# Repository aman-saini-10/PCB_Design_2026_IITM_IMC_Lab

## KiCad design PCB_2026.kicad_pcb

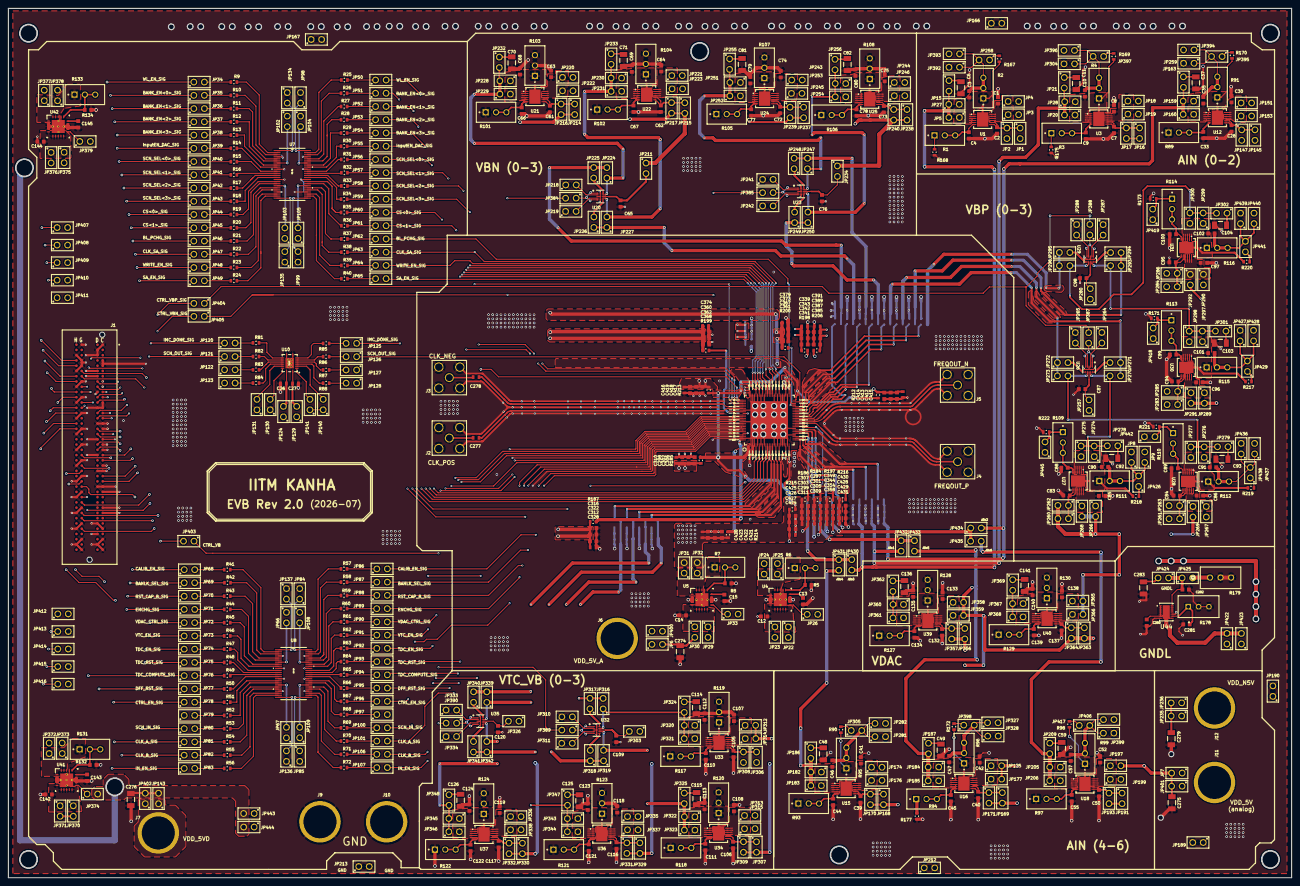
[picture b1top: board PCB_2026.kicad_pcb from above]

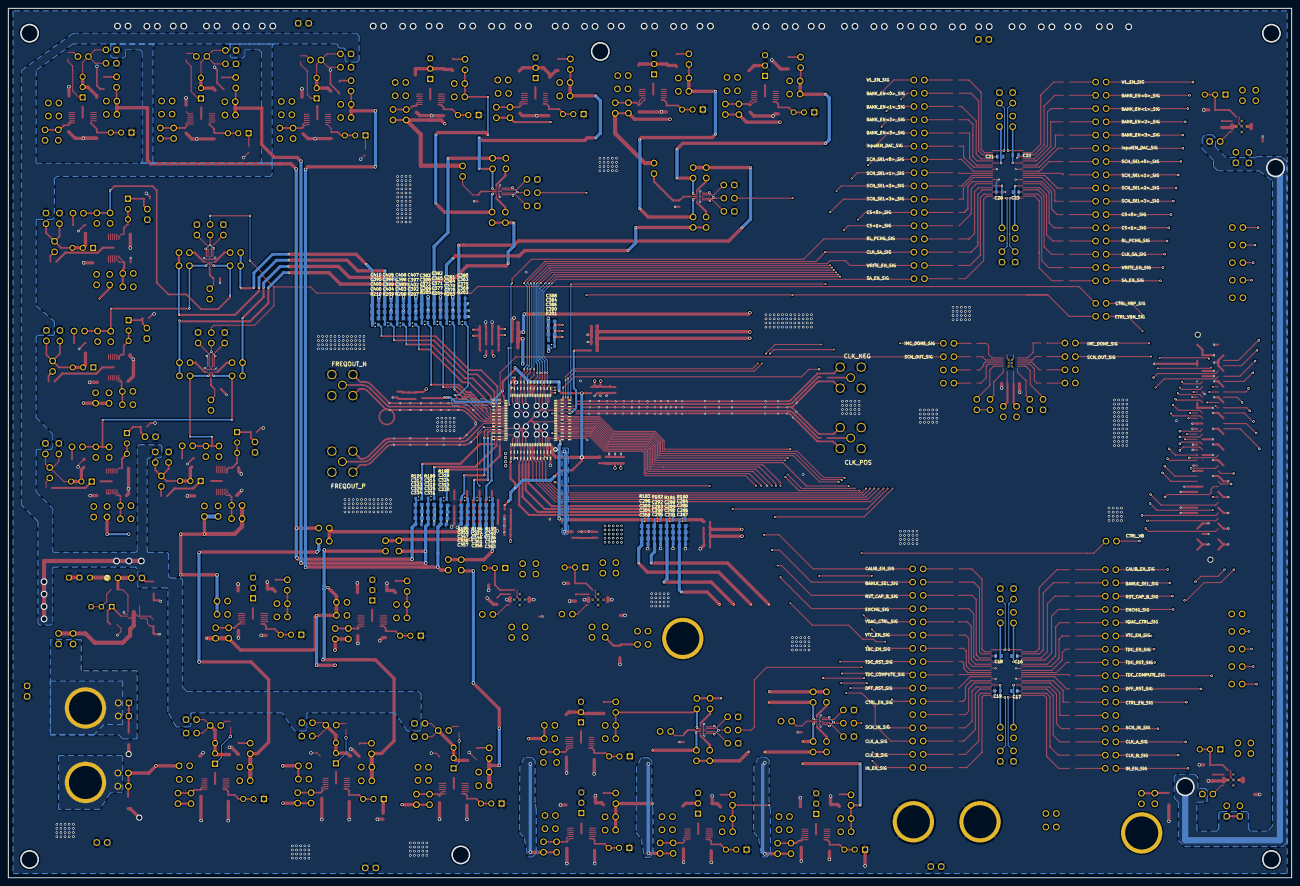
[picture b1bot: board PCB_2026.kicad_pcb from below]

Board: 4 copper layers, 310.0 x 210.0 mm, 859 parts (103 on the bottom side), 512 nets.

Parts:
C1, C3, C8, C10, C30, C35, C41, C42, C46, C47, C52, C57, C63, C64, C68, C69, C74, C75, C79, C80, C85, C86, C90, C91, C96, C97, C101, C102, C107, C108, C112, C113, C118, C119, C123, C124, C133, C135, C138, C140, C280, C282: 10u; CAPC1608X90N
C2, C7, C12, C14, C28, C39, C40, C50, C61, C62, C72, C73, C83, C84, C94, C95, C105, C106, C116, C117, C132, C137, C142, C144: 4.7u; CAPC1608X90N
C4, C9, C33, C44, C45, C55, C65, C66, C67, C76, C77, C78, C87, C88, C89, C98, C99, C100, C109, C110, C111, C120, C121, C122, C134, C139, C281, C285, C289, C293, C300, C301, C302, C303, C316, C318, C319, C323, C340, C341, C346, C347, C349, C362, C367, C369, C370, C371, C372, C386, C387, C397, C398, C399, C400, C413, C418, C421, C426, C429: 100n; CAPC1608X90N
C6, C11, C37, C48, C49, C59, C70, C71, C81, C82, C92, C93, C103, C104, C114, C115, C125, C126, C136, C141, C274, C275, C276, C279, C283: C100u; CAPC3216X180N
C13, C15, C143, C145, C286, C290, C294, C304, C305, C306, C307, C322, C324, C325, C329, C342, C348, C351, C352, C354, C368, C373, C375, C376, C377, C378, C388, C389, C402, C403, C404, C405, C414, C417, C422, C425, C430: 1n; CAPC1608X90N
C16, C17, C18, C19, C20, C21, C22, C23, C26, C27: 1uF; CAPC1608X90N
C277, C278, C287, C291, C295, C308, C309, C310, C311, C328, C330, C331, C334, C339, C353, C356, C357, C358, C374, C379, C380, C381, C382, C383, C390, C391, C407, C408, C409, C410, C415, C416, C420, C424, C431: 1u; CAPC1608X90N
C284, C288, C292, C296, C297, C298, C299, C312, C313, C314, C317, C336, C337, C338, C343, C344, C360, C361, C363, C364, C365, C366, C384, C385, C392, C393, C394, C395, C412, C419, C423, C427, C428: 10n; CAPC1608X90N
J1: ASP-134603-01; CONN160_4603-01_SAI
J2, J3, J4, J5: 142-0701-201; CONN_142-0701-201_CIN
J6, J7, J9, J10, J11, J12: BJACK
JP1, JP2, JP3, JP4, JP5, JP6, JP7, JP8, JP9, JP15, JP16, JP17, JP18, JP19, JP20, JP21, JP22, JP23, JP24, JP25, JP26, JP27, JP28, JP29, JP30, JP31, JP32, JP33, JP34, JP35, JP36, JP37, JP38, JP39, JP40, JP41, JP42, JP43, JP44, JP45, JP46, JP47, JP48, JP49, JP50, JP51, JP52, JP53, JP54, JP55, JP56, JP57, JP58, JP59, JP60, JP61, JP62, JP63, JP64, JP65, JP66, JP67, JP68, JP69, JP70, JP71, JP72, JP73, JP74, JP75, JP76, JP77, JP78, JP79, JP80, JP81, JP82, JP83, JP84, JP85, JP86, JP87, JP88, JP89, JP90, JP91, JP92, JP93, JP94, JP95, JP96, JP97, JP98, JP99, JP100, JP101, JP102, JP103, JP104, JP105, JP106, JP107, JP108, JP109, JP120, JP121, JP122, JP123, JP124, JP125, JP126, JP127, JP128, JP129, JP130, JP131, JP134, JP135, JP136, JP137, JP140, JP141, JP143, JP145, JP147, JP151, JP153, JP159, JP160, JP163, JP166, JP167, JP168, JP169, JP170, JP171, JP174, JP175, JP176, JP177, JP182, JP183, JP184, JP185, JP186, JP187, JP189, JP190, JP191, JP193, JP197, JP199, JP205, JP206, JP209, JP211, JP212, JP213, JP214, JP215, JP216, JP217, JP218, JP219, JP220, JP221, JP222, JP223, JP224, JP225, JP226, JP227, JP228, JP229, JP230, JP231, JP232, JP233, JP234, JP235, JP236, JP237, JP238, JP239, JP240, JP241, JP242, JP243, JP244, JP245, JP246, JP247, JP248, JP249, JP250, JP251, JP252, JP253, JP254, JP255, JP256, JP257, JP258, JP259, JP260, JP261, JP262, JP263, JP264, JP265, JP266, JP267, JP268, JP269, JP270, JP271, JP272, JP273, JP274, JP275, JP276, JP277, JP278, JP279, JP280, JP281, JP282, JP283, JP284, JP285, JP286, JP287, JP288, JP289, JP290, JP291, JP292, JP293, JP294, JP295, JP296, JP297, JP298, JP299, JP300, JP301, JP302, JP303, JP304, JP305, JP306, JP307, JP308, JP309, JP310, JP311, JP312, JP313, JP314, JP315, JP316, JP317, JP318, JP319, JP320, JP321, JP322, JP323, JP324, JP325, JP326, JP327, JP328, JP329, JP330, JP331, JP332, JP333, JP334, JP335, JP336, JP337, JP338, JP339, JP340, JP341, JP342, JP343, JP344, JP345, JP346, JP347, JP348, JP356, JP357, JP358, JP359, JP360, JP361, JP362, JP363, JP364, JP365, JP366, JP367, JP368, JP369, JP370, JP371, JP372, JP373, JP374, JP375, JP376, JP377, JP378, JP379, JP384, JP385, JP387, JP388, JP389, JP390, JP392, JP393, JP394, JP395, JP396, JP397, JP398, JP399, JP400, JP401, JP402, JP403, JP404, JP405, JP406, JP407, JP408, JP409, JP410, JP411, JP412, JP413, JP414, JP415, JP416, JP417, JP418, JP419, JP422, JP423, JP424, JP425, JP426, JP427, JP428, JP429, JP430, JP431, JP432, JP433, JP434, JP435, JP436, JP437, JP438, JP439, JP440, JP441, JP442, JP443, JP444, JP445: Jumper; 61300211121
R1, R3, R89, R93, R109, R110, R113, R114: 5kOhms; TRIM_PV36W253C01B00
R2, R4, R91, R95, R96, R99, R103, R104, R107, R108, R111, R112, R115, R116, R119, R120, R123, R124, R128, R130, R131, R133: 5kOhms; TRIM_PV36W502C01B00
R5, R8, R132, R134: 1kOhm; RESC1508X50N
R6: 2kOhms; TRIM_PV36W253C01B00
R7: 200 Ohms; TRIM_PV36W253C01B00
R9, R10, R11, R12, R13, R14, R15, R16, R17, R18, R19, R20, R21, R22, R23, R24, R25, R26, R27, R28, R29, R30, R31, R32, R33, R34, R35, R36, R37, R38, R39, R40, R41, R42, R43, R44, R45, R46, R47, R48, R49, R50, R51, R52, R53, R54, R55, R56, R57, R58, R59, R60, R62, R63, R64, R65, R66, R67, R68, R69, R70, R71, R72, R81, R82, R83, R84, R85, R86, R87, R88: 10 ohm 1%; RES_ERJ3EKF10R0V
R61, R180, R181, R182, R183, R184, R185, R186, R187, R188, R189, R191, R193, R194, R195, R197, R198, R199, R200, R201, R202, R203, R204, R205, R206, R207, R208, R209, R210, R212, R213, R214, R215, R216: 1 ohm 0603; RES_ERJ3EKF10R0V
R90, R98, R167, R169, R170, R172, R217, R218, R219, R220: 10 ohm; RES_ERJ3EKF10R0V
R94, R97: 1kOhms; TRIM_PV36W253C01B00
R101, R102, R105, R106, R117, R118, R121, R122, R127, R129: 25kOhms; TRIM_PV36W253C01B00
R168: 5k ohm; RES_ERJ3EKF10R0V
R171, R173, R221, R222: 2k ohm; RES_ERJ3EKF10R0V
R175: 3k ohm; RES_ERJ3EKF10R0V
R177: 0.5k ohm; RES_ERJ3EKF10R0V
R178: PV36W203C01B00; POT_PV36W_MUR
R179: PV36W503C01B00; RES_PV36W503C01B00_BRN
U1, U3, U12, U15, U16, U18, U21, U22, U24, U25, U27, U28, U30, U31, U33, U34, U36, U37, U39, U40: LT3083EDF-PBF; DFN-12_DF_LIT
U4, U5, U41, U42: TPS74401RGWT; RGW0020A
U7, U8: SN74AVCH16T245GR; DGG48
U10: SN74AVC4T245RGYR; RGY16_2P55X2P05
U20, U23, U26, U29, U32, U35: TMUX1072RUTR; RUT0012A-MFG
U43: QFN100_0p8mm_lead
U44: LT3091EDE-TRPBF; DE_14_ADI

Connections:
/AIN0: C313.1, C318.1, C324.1, C330.1, JP5.2, JP15.2, JP27.1, JP430.2, R188.1
/AIN0_LS: C3.1, JP5.1, JP27.2, R2.1, R167.2, U1.1 (OUT), U1.2 (OUT), U1.3 (OUT), U1.4 (OUT), U1.5 (OUT), U1.13 (EPAD)
/AIN1: C314.1, C319.1, C325.1, C331.1, JP20.2, JP21.2, JP28.1, JP432.2, R189.1
/AIN1_LS: C10.1, JP20.1, JP28.2, R4.1, R169.2, U3.1 (OUT), U3.2 (OUT), U3.3 (OUT), U3.4 (OUT), U3.5 (OUT), U3.13 (EPAD)
/AIN2: C317.1, C323.1, C329.1, C334.1, JP159.2, JP160.1, JP163.2, JP434.2, R191.1
/AIN2_LS: C35.1, JP159.1, JP160.2, R91.1, R170.2, U12.1 (OUT), U12.2 (OUT), U12.3 (OUT), U12.4 (OUT), U12.5 (OUT), U12.13 (EPAD)
/AIN4: JP182.2, JP183.1, JP186.2, JP431.2
/AIN4_LS: C46.1, JP182.1, JP183.2, R90.2, R95.1, U15.1 (OUT), U15.2 (OUT), U15.3 (OUT), U15.4 (OUT), U15.5 (OUT), U15.13 (EPAD)
/AIN5: JP184.2, JP185.1, JP187.2, JP433.2
/AIN5_LS: C47.1, JP184.1, JP185.2, R96.1, R172.2, U16.1 (OUT), U16.2 (OUT), U16.3 (OUT), U16.4 (OUT), U16.5 (OUT), U16.13 (EPAD)
/AIN6: JP205.2, JP206.1, JP209.2, JP435.2
/AIN6_LS: C57.1, JP205.1, JP206.2, R98.2, R99.1, U18.1 (OUT), U18.2 (OUT), U18.3 (OUT), U18.4 (OUT), U18.5 (OUT), U18.13 (EPAD)
/BANK_EN<0>_Q: JP51.2, U43.13 (BANK_EN<0>)
/BANK_EN<0>_SIG: J1.11, JP35.1
/BANK_EN<1>_Q: JP52.2, U43.12 (BANK_EN<1>)
/BANK_EN<1>_SIG: J1.14, JP36.1
/BANK_EN<2>_Q: JP53.2, U43.11 (BANK_EN<2>)
/BANK_EN<2>_SIG: J1.15, JP37.1
/BANK_EN<3>_Q: JP54.2, U43.9 (BANK_EN<3>)
/BANK_EN<3>_SIG: J1.18, JP38.1
/BANK_SEL_Q: JP87.2, U43.97 (BANK_SEL)
/BANK_SEL_SIG: J1.58, JP69.1
/BL_PCHG_Q: JP62.2, U43.51 (BL_PCHG)
/BL_PCHG_SIG: J1.22, JP46.1
/CALIB_EN_Q: JP86.2, U43.98 (CALIB_EN)
/CALIB_EN_SIG: J1.57, JP68.1
/CLK_+: C277.2, U43.81 (CLK_POS)
/CLK_-: C278.2, U43.80 (CLK_NEG)
/CLK_A_Q: JP101.2, U43.79 (CLK_A)
/CLK_A_SIG: J1.104, JP81.1
/CLK_B_Q: JP106.2, U43.78 (CLK_B)
/CLK_B_SIG: J1.105, JP82.1
/CLK_SA_Q: JP63.2, U43.57 (CLK_SA_B)
/CLK_SA_SIG: J1.23, JP47.1
/CLK_conn_+: C277.1, J2.1
/CLK_conn_-: C278.1, J3.1
/CS<0>_Q: JP60.2, U43.67 (CS<0>)
/CS<0>_SIG: J1.54, JP44.1
/CS<1>_Q: JP61.2, U43.65 (CS<1>)
/CS<1>_SIG: J1.55, JP45.1
/CTRL_EN_Q: JP96.2, U43.85 (CTRL_EN)
/CTRL_EN_SIG: J1.102, JP78.1
/CTRL_VB: JP389.2, JP390.2, JP403.1
/CTRL_VBN: JP384.2, JP385.2, JP405.1
/CTRL_VBN_SIG: J1.116, JP405.2
/CTRL_VBP: JP387.2, JP388.2, JP404.1
/CTRL_VBP_SIG: J1.114, JP404.2
/CTRL_VB_SIG: J1.113, JP403.2
/DFF_RST_Q: JP95.2, U43.86 (DFF_RST)
/DFF_RST_SIG: J1.92, JP77.1
/ENCHG_Q: JP89.2, U43.93 (CHG_EN)
/ENCHG_SIG: J1.61, JP71.1
/EN_U4: JP26.1, U4.11 (EN)
/EN_U5: JP33.1, U5.11 (EN)
/EN_U41: JP374.1, U41.11 (EN)
/EN_U42: JP379.1, U42.11 (EN)
/FREQOUT_N: J5.1, U43.37 (FreqOut_Neg)
/FREQOUT_P: J4.1, U43.36 (FreqOut_Pos)
/GNDL: C282.1, JP424.1, JP425.1, U44.11 (OUT), U44.12 (OUT), U44.13 (OUT), U44.14 (OUT)
/GNDL_BUF: C283.1, JP9.2, JP282.2, JP328.2, JP393.2, JP394.2, JP396.2, JP406.2, JP424.2, JP428.2, JP437.2, JP440.2
/GNDL_JP: JP425.2, R179.1
/H4: J1.124, JP407.1
/H5: J1.125, JP408.1
/H7: J1.127, JP409.1
/H8: J1.128, JP410.1
/H10: J1.130, JP411.1
/H11: J1.131, JP412.1
/H13: J1.133, JP413.1
/H14: J1.134, JP414.1
/H16: J1.136, JP415.1
/H17: J1.137, JP416.1
/IMC_DONE_Q: JP125.1, U43.95 (IMC_DONE)
/IMC_DONE_SIG: J1.110, JP120.1
/IN_EN_Q: JP107.2, U43.77 (IN_EN)
/IN_EN_SIG: J1.107, JP83.1
/InputEN_DAC_Q: JP55.2, U43.34 (InputEN_DAC)
/InputEN_DAC_SIG: J1.19, JP39.1
/RST_CAP_B_Q: JP88.2, U43.94 (RST_CAP_B)
/RST_CAP_B_SIG: J1.60, JP70.1
/SA_EN_Q: JP65.2, U43.69 (SA_EN_B)
/SA_EN_SIG: J1.27, JP49.1
/SCN_IN_Q: JP100.2, U43.76 (SCN_IN)
/SCN_IN_SIG: J1.108, JP80.1
/SCN_OUT_Q: JP126.1, U43.49 (SCN_OUT)
/SCN_OUT_SIG: J1.111, JP121.1
/SCN_SEL<0>_Q: JP56.2, U43.64 (SCN_SEL<0>)
/SCN_SEL<0>_SIG: J1.48, JP40.1
/SCN_SEL<1>_Q: JP57.2, U43.63 (SCN_SEL<1>)
/SCN_SEL<1>_SIG: J1.49, JP41.1
/SCN_SEL<2>_Q: JP58.2, U43.62 (SCN_SEL<2>)
/SCN_SEL<2>_SIG: J1.51, JP42.1
/SCN_SEL<3>_Q: JP59.2, U43.61 (SCN_SEL<3>)
/SCN_SEL<3>_SIG: J1.52, JP43.1
/TDC_COMPUTE_Q: JP94.2, U43.87 (TDC_COMPUTE)
/TDC_COMPUTE_SIG: J1.93, JP76.1
/TDC_EN_Q: JP92.2, U43.90 (TDC_EN)
/TDC_EN_SIG: J1.89, JP74.1
/TDC_RST_Q: JP93.2, U43.88 (TDC_RST_B)
/TDC_RST_SIG: J1.90, JP75.1
/U1_IN: C1.1, JP3.1, JP4.1, U1.9 (IN), U1.10 (IN), U1.11 (IN), U1.12 (IN)
/U1_SET: C4.2, R1.2, R1.3, U1.6 (SET)
/U1_VCONTROL: C2.1, JP1.1, JP2.1, U1.7 (VCONTROL), U1.8 (VCONTROL)
/U3_IN: C8.1, JP18.1, JP19.1, U3.9 (IN), U3.10 (IN), U3.11 (IN), U3.12 (IN)
/U3_SET: C9.2, R3.2, R3.3, U3.6 (SET)
/U3_VCONTROL: C7.1, JP16.1, JP17.1, U3.7 (VCONTROL), U3.8 (VCONTROL)
/U12_IN: C30.1, JP151.1, JP153.1, U12.9 (IN), U12.10 (IN), U12.11 (IN), U12.12 (IN)
/U12_SET: C33.2, R89.2, R89.3, U12.6 (SET)
/U12_VCONTROL: C28.1, JP145.1, JP147.1, U12.7 (VCONTROL), U12.8 (VCONTROL)
/U15_IN: C41.1, JP174.1, JP176.1, U15.9 (IN), U15.10 (IN), U15.11 (IN), U15.12 (IN)
/U15_SET: C44.2, R93.2, R93.3, U15.6 (SET)
/U15_VCONTROL: C39.1, JP168.1, JP170.1, U15.7 (VCONTROL), U15.8 (VCONTROL)
/U16_IN: C42.1, JP175.1, JP177.1, U16.9 (IN), U16.10 (IN), U16.11 (IN), U16.12 (IN)
/U16_SET: C45.2, R94.2, R94.3, U16.6 (SET)
/U16_VCONTROL: C40.1, JP169.1, JP171.1, U16.7 (VCONTROL), U16.8 (VCONTROL)
/U18_IN: C52.1, JP197.1, JP199.1, U18.9 (IN), U18.10 (IN), U18.11 (IN), U18.12 (IN)
/U18_SET: C55.2, R97.2, R97.3, U18.6 (SET)
/U18_VCONTROL: C50.1, JP191.1, JP193.1, U18.7 (VCONTROL), U18.8 (VCONTROL)
/U21_IN: C63.1, JP220.1, JP222.1, U21.9 (IN), U21.10 (IN), U21.11 (IN), U21.12 (IN)
/U21_OUT: C68.1, JP228.1, JP229.2, R103.1, U21.1 (OUT), U21.2 (OUT), U21.3 (OUT), U21.4 (OUT), U21.5 (OUT), U21.13 (EPAD)
/U21_SET: C66.2, R101.2, R101.3, U21.6 (SET)
/U21_VCONTROL: C61.1, JP214.1, JP216.1, U21.7 (VCONTROL), U21.8 (VCONTROL)
/U22_IN: C64.1, JP221.1, JP223.1, U22.9 (IN), U22.10 (IN), U22.11 (IN), U22.12 (IN)
/U22_OUT: C69.1, JP230.1, JP231.2, R104.1, U22.1 (OUT), U22.2 (OUT), U22.3 (OUT), U22.4 (OUT), U22.5 (OUT), U22.13 (EPAD)
/U22_SET: C67.2, R102.2, R102.3, U22.6 (SET)
/U22_VCONTROL: C62.1, JP215.1, JP217.1, U22.7 (VCONTROL), U22.8 (VCONTROL)
/U24_IN: C74.1, JP243.1, JP245.1, U24.9 (IN), U24.10 (IN), U24.11 (IN), U24.12 (IN)
/U24_OUT: C79.1, JP251.1, JP252.2, R107.1, U24.1 (OUT), U24.2 (OUT), U24.3 (OUT), U24.4 (OUT), U24.5 (OUT), U24.13 (EPAD)
/U24_SET: C77.2, R105.2, R105.3, U24.6 (SET)
/U24_VCONTROL: C72.1, JP237.1, JP239.1, U24.7 (VCONTROL), U24.8 (VCONTROL)
/U25_IN: C75.1, JP244.1, JP246.1, U25.9 (IN), U25.10 (IN), U25.11 (IN), U25.12 (IN)
/U25_OUT: C80.1, JP253.1, JP254.2, R108.1, U25.1 (OUT), U25.2 (OUT), U25.3 (OUT), U25.4 (OUT), U25.5 (OUT), U25.13 (EPAD)
/U25_SET: C78.2, R106.2, R106.3, U25.6 (SET)
/U25_VCONTROL: C73.1, JP238.1, JP240.1, U25.7 (VCONTROL), U25.8 (VCONTROL)
/U27_IN: C85.1, JP266.1, JP268.1, U27.9 (IN), U27.10 (IN), U27.11 (IN), U27.12 (IN)
/U27_OUT: C90.1, JP274.1, JP275.2, R111.1, R218.2, U27.1 (OUT), U27.2 (OUT), U27.3 (OUT), U27.4 (OUT), U27.5 (OUT), U27.13 (EPAD)
/U27_SET: C88.2, R109.2, R109.3, U27.6 (SET)
/U27_VCONTROL: C83.1, JP260.1, JP262.1, U27.7 (VCONTROL), U27.8 (VCONTROL)
/U28_IN: C86.1, JP267.1, JP269.1, U28.9 (IN), U28.10 (IN), U28.11 (IN), U28.12 (IN)
/U28_OUT: C91.1, JP276.1, JP277.2, R112.1, R219.2, U28.1 (OUT), U28.2 (OUT), U28.3 (OUT), U28.4 (OUT), U28.5 (OUT), U28.13 (EPAD)
/U28_SET: C89.2, R110.2, R110.3, U28.6 (SET)
/U28_VCONTROL: C84.1, JP261.1, JP263.1, U28.7 (VCONTROL), U28.8 (VCONTROL)
/U30_IN: C96.1, JP289.1, JP291.1, U30.9 (IN), U30.10 (IN), U30.11 (IN), U30.12 (IN)
/U30_OUT: C101.1, JP297.1, JP298.2, R115.1, R217.2, U30.1 (OUT), U30.2 (OUT), U30.3 (OUT), U30.4 (OUT), U30.5 (OUT), U30.13 (EPAD)
/U30_SET: C99.2, R113.2, R113.3, U30.6 (SET)
/U30_VCONTROL: C94.1, JP283.1, JP285.1, U30.7 (VCONTROL), U30.8 (VCONTROL)
/U31_IN: C97.1, JP290.1, JP292.1, U31.9 (IN), U31.10 (IN), U31.11 (IN), U31.12 (IN)
/U31_OUT: C102.1, JP299.1, JP300.2, R116.1, R220.2, U31.1 (OUT), U31.2 (OUT), U31.3 (OUT), U31.4 (OUT), U31.5 (OUT), U31.13 (EPAD)
/U31_SET: C100.2, R114.2, R114.3, U31.6 (SET)
/U31_VCONTROL: C95.1, JP284.1, JP286.1, U31.7 (VCONTROL), U31.8 (VCONTROL)
/U33_IN: C107.1, JP312.1, JP314.1, U33.9 (IN), U33.10 (IN), U33.11 (IN), U33.12 (IN)
/U33_OUT: C112.1, JP320.1, JP321.2, R119.1, U33.1 (OUT), U33.2 (OUT), U33.3 (OUT), U33.4 (OUT), U33.5 (OUT), U33.13 (EPAD)
/U33_SET: C110.2, R117.2, R117.3, U33.6 (SET)
/U33_VCONTROL: C105.1, JP306.1, JP308.1, U33.7 (VCONTROL), U33.8 (VCONTROL)
/U34_IN: C108.1, JP313.1, JP315.1, U34.9 (IN), U34.10 (IN), U34.11 (IN), U34.12 (IN)
/U34_OUT: C113.1, JP322.1, JP323.2, R120.1, U34.1 (OUT), U34.2 (OUT), U34.3 (OUT), U34.4 (OUT), U34.5 (OUT), U34.13 (EPAD)
/U34_SET: C111.2, R118.2, R118.3, U34.6 (SET)
/U34_VCONTROL: C106.1, JP307.1, JP309.1, U34.7 (VCONTROL), U34.8 (VCONTROL)
/U36_IN: C118.1, JP335.1, JP337.1, U36.9 (IN), U36.10 (IN), U36.11 (IN), U36.12 (IN)
/U36_OUT: C123.1, JP343.1, JP344.2, R123.1, U36.1 (OUT), U36.2 (OUT), U36.3 (OUT), U36.4 (OUT), U36.5 (OUT), U36.13 (EPAD)
/U36_SET: C121.2, R121.2, R121.3, U36.6 (SET)
/U36_VCONTROL: C116.1, JP329.1, JP331.1, U36.7 (VCONTROL), U36.8 (VCONTROL)
/U37_IN: C119.1, JP336.1, JP338.1, U37.9 (IN), U37.10 (IN), U37.11 (IN), U37.12 (IN)
/U37_OUT: C124.1, JP345.1, JP346.2, R124.1, U37.1 (OUT), U37.2 (OUT), U37.3 (OUT), U37.4 (OUT), U37.5 (OUT), U37.13 (EPAD)
/U37_SET: C122.2, R122.2, R122.3, U37.6 (SET)
/U37_VCONTROL: C117.1, JP330.1, JP332.1, U37.7 (VCONTROL), U37.8 (VCONTROL)
/U39_IN: C133.1, JP358.1, JP359.1, U39.9 (IN), U39.10 (IN), U39.11 (IN), U39.12 (IN)
/U39_OUT: C135.1, JP360.1, JP361.2, R128.1, U39.1 (OUT), U39.2 (OUT), U39.3 (OUT), U39.4 (OUT), U39.5 (OUT), U39.13 (EPAD)
/U39_SET: C134.2, R127.2, R127.3, U39.6 (SET)
/U39_VCONTROL: C132.1, JP356.1, JP357.1, U39.7 (VCONTROL), U39.8 (VCONTROL)
/U40_IN: C138.1, JP365.1, JP366.1, U40.9 (IN), U40.10 (IN), U40.11 (IN), U40.12 (IN)
/U40_OUT: C140.1, JP367.1, JP368.2, R130.1, U40.1 (OUT), U40.2 (OUT), U40.3 (OUT), U40.4 (OUT), U40.5 (OUT), U40.13 (EPAD)
/U40_SET: C139.2, R129.2, R129.3, U40.6 (SET)
/U40_VCONTROL: C137.1, JP363.1, JP364.1, U40.7 (VCONTROL), U40.8 (VCONTROL)
/U44_SET: C281.1, R178.1, U44.9 (SET)
/VB0: C284.1, C285.1, C286.1, C287.1, JP316.2, JP317.2, R180.1
/VB0_MUX: JP316.1, JP320.2, JP321.1, JP324.2, U32.10 (NC1)
/VB1: C288.1, C289.1, C290.1, C291.1, JP318.1, JP319.1, R181.1
/VB1_MUX: JP319.2, JP322.2, JP323.1, JP325.2, U32.8 (NC2)
/VB2: C292.1, C293.1, C294.1, C295.1, JP339.2, JP340.2, R182.1
/VB2_MUX: JP339.1, JP343.2, JP344.1, JP347.2, U35.10 (NC1)
/VB3: C296.1, C300.1, C304.1, C308.1, JP341.1, JP342.1, R183.1
/VB3_MUX: JP342.2, JP345.2, JP346.1, JP348.2, U35.8 (NC2)
/VBN0: C363.1, C369.1, C375.1, C380.1, JP224.2, JP225.2, R202.1
/VBN0_MUX: JP224.1, JP228.2, JP229.1, JP232.2, U20.10 (NC1)
/VBN0_q: R202.2, U43.39 (VBN<0>)
/VBN1: C364.1, C370.1, C376.1, C381.1, JP226.1, JP227.1, R203.1
/VBN1_MUX: JP227.2, JP230.2, JP231.1, JP233.2, U20.8 (NC2)
/VBN1_q: R203.2, U43.40 (VBN<1>)
/VBN2: C365.1, C371.1, C377.1, C382.1, JP247.2, JP248.2, R204.1
/VBN2_MUX: JP247.1, JP251.2, JP252.1, JP255.2, U23.10 (NC1)
/VBN2_q: R204.2, U43.41 (VBN<2>)
/VBN3: C366.1, C372.1, C378.1, C383.1, JP249.1, JP250.1, R205.1
/VBN3_MUX: JP250.2, JP253.2, JP254.1, JP256.2, U23.8 (NC2)
/VBN3_q: R205.2, U43.42 (VBN<3>)
/VBP0: C392.1, C397.1, C402.1, C407.1, JP270.2, JP271.2, R207.2
/VBP0_MUX: JP270.1, JP274.2, JP275.1, JP278.2, U26.10 (NC1)
/VBP0_q: R207.1, U43.43 (VBP<0>)
/VBP1: C393.1, C398.1, C403.1, C408.1, JP272.1, JP273.1, R208.2
/VBP1_MUX: JP273.2, JP276.2, JP277.1, JP279.2, U26.8 (NC2)
/VBP1_q: R208.1, U43.44 (VBP<1>)
/VBP2: C394.1, C399.1, C404.1, C409.1, JP293.2, JP294.2, R209.2
/VBP2_MUX: JP293.1, JP297.2, JP298.1, JP301.2, U29.10 (NC1)
/VBP2_q: R209.1, U43.45 (VBP<2>)
/VBP3: C395.1, C400.1, C405.1, C410.1, JP295.1, JP296.1, R210.2
/VBP3_MUX: JP296.2, JP299.2, JP300.1, JP302.2, U29.8 (NC2)
/VBP3_q: R210.1, U43.46 (VBP<3>)
/VCCA_DIG_LS: JP104.1, JP105.1, JP108.1, JP109.1, JP129.1, JP140.1, JP141.1, JP372.2, JP373.2
/VCCB_DIG_LS: JP66.1, JP67.1, JP102.1, JP103.1, JP124.1, JP377.2, JP378.2
/VDAC: C312.1, C316.1, C322.1, C328.1, C360.1, C361.1, C362.1, C367.1, C368.1, C373.1, C374.1, C379.1, JP360.2, JP361.1, JP362.2, JP367.2, JP368.1, JP369.2, R187.1, R199.2, R200.2
/VDAC_CTRL_Q: JP90.2, U43.92 (VDAC_CTRL)
/VDAC_CTRL_SIG: J1.86, JP72.1
/VDDA_0.9V: C297.1, C299.1, C301.1, C303.1, C305.1, C307.1, C309.1, C311.1, C339.1, C341.1, C342.1, C343.1, C344.1, C349.1, C354.1, C358.1, C384.1, C385.1, C386.1, C387.1, C388.1, C389.1, C390.1, C391.1, C420.1, C421.1, C422.1, C423.1, C428.1, C429.1, C430.1, C431.1, JP31.2, JP32.2, R184.1, R186.1, R197.2, R198.1, R201.2, R206.2, R214.1, R216.2
/VDDA_chip: R184.2, R186.2, R197.1, R198.2, R201.1, R206.1, R214.2, R216.1, U43.5 (vdda), U43.23 (vdda), U43.35 (vdda), U43.48 (vdda), U43.53 (vdda), U43.75 (vdda), U43.84 (vdda), U43.96 (vdda)
/VDDQ_1.8V: C298.1, C302.1, C306.1, C310.1, C412.1, C413.1, C414.1, C415.1, C416.1, C417.1, C418.1, C419.1, C424.1, C425.1, C426.1, C427.1, JP24.2, JP25.2, R185.1, R212.1, R213.1, R215.1
/VDDQ_chip: R185.2, R212.2, R213.2, R215.2, U43.1 (vddq), U43.25 (vddq), U43.50 (vddq), U43.71 (vddq)
/VDD_5V: C275.1, JP1.2, JP2.2, JP3.2, JP4.2, JP7.2, JP16.2, JP17.2, JP18.2, JP19.2, JP145.2, JP147.2, JP151.2, JP153.2, JP168.2, JP169.2, JP170.2, JP171.2, JP174.2, JP175.2, JP176.2, JP177.2, JP191.2, JP193.2, JP197.2, JP199.2, JP211.1, JP214.2, JP215.2, JP216.2, JP217.2, JP220.2, JP221.2, JP222.2, JP223.2, JP234.1, JP237.2, JP238.2, JP239.2, JP240.2, JP243.2, JP244.2, JP245.2, JP246.2, JP257.1, JP260.2, JP261.2, JP262.2, JP263.2, JP266.2, JP267.2, JP268.2, JP269.2, JP280.1, JP283.2, JP284.2, JP285.2, JP286.2, JP289.2, JP290.2, JP291.2, JP292.2, JP303.1, JP306.2, JP307.2, JP308.2, JP309.2, JP312.2, JP313.2, JP314.2, JP315.2, JP326.1, JP329.2, JP330.2, JP331.2, JP332.2, JP335.2, JP336.2, JP337.2, JP338.2, JP356.2, JP357.2, JP358.2, JP359.2, JP363.2, JP364.2, JP365.2, JP366.2, JP401.2, JP443.1, JP444.1
/VDD_5VD: C276.1, JP143.2, JP370.2, JP371.2, JP374.2, JP375.2, JP376.2, JP379.2, JP402.2, JP443.2, JP444.2
/VDD_5VD_JACK: J7.1, JP143.1, JP402.1
/VDD_5V_JACK: J11.1, JP7.1, JP401.1
/VDD_5V_U4: C12.1, JP22.1, JP23.1, U4.5 (IN), U4.6 (IN), U4.7 (IN), U4.8 (IN), U4.10 (BIAS)
/VDD_5V_U5: C14.1, JP29.1, JP30.1, U5.5 (IN), U5.6 (IN), U5.7 (IN), U5.8 (IN), U5.10 (BIAS)
/VDD_5V_U41: C142.1, JP370.1, JP371.1, U41.5 (IN), U41.6 (IN), U41.7 (IN), U41.8 (IN), U41.10 (BIAS)
/VDD_5V_U42: C144.1, JP375.1, JP376.1, U42.5 (IN), U42.6 (IN), U42.7 (IN), U42.8 (IN), U42.10 (BIAS)
/VDD_5V_a: C274.1, JP6.2, JP22.2, JP23.2, JP26.2, JP29.2, JP30.2, JP33.2, JP400.2
/VDD_5V_a_JACK: J6.1, JP6.1, JP400.1
/VDD_N5V: C279.1, JP235.2, JP236.2, JP422.1, JP423.1
/VDD_N5V_JACK: J12.1, JP235.1, JP236.1
/VFB_U4: R5.2, R6.2, R6.3, U4.16 (FB)
/VFB_U5: R7.2, R7.3, R8.2, U5.16 (FB)
/VFB_U41: R131.2, R131.3, R132.2, U41.16 (FB)
/VFB_U42: R133.2, R133.3, R134.2, U42.16 (FB)
/VIN_U44: C280.1, JP422.2, JP423.2, U44.1 (IN), U44.2 (IN), U44.3 (IN), U44.4 (IN), U44.5 (ILIM), U44.6 (IMONP), U44.8 (*SHDN), U44.15 (IN)
/VOUT_U4: JP24.1, JP25.1, R6.1, U4.1 (OUT), U4.18 (OUT), U4.19 (OUT), U4.20 (OUT)
/VOUT_U5: JP31.1, JP32.1, R7.1, U5.1 (OUT), U5.18 (OUT), U5.19 (OUT), U5.20 (OUT)
/VOUT_U41: JP372.1, JP373.1, R131.1, U41.1 (OUT), U41.18 (OUT), U41.19 (OUT), U41.20 (OUT)
/VOUT_U42: JP377.1, JP378.1, R133.1, U42.1 (OUT), U42.18 (OUT), U42.19 (OUT), U42.20 (OUT)
/VTC_EN_Q: JP91.2, U43.91 (VTC_EN)
/VTC_EN_SIG: J1.87, JP73.1
/WL_EN_Q: JP50.2, U43.7 (WL_EN)
/WL_EN_SIG: J1.10, JP34.1
/WRITE_EN_Q: JP64.2, U43.59 (WRITE_EN)
/WRITE_EN_SIG: J1.26, JP48.1
GND: C1.2, C2.2, C4.1, C6.2, C7.2, C8.2, C9.1, C11.2, C12.2, C13.2, C14.2, C15.2, C16.2, C17.2, C18.2, C19.2, C20.2, C21.2, C22.2, C23.2, C26.2, C27.2, C28.2, C30.2, C33.1, C37.2, C39.2, C40.2, C41.2, C42.2, C44.1, C45.1, C48.2, C49.2, C50.2, C52.2, C55.1, C59.2, C61.2, C62.2, C63.2, C64.2, C65.2, C66.1, C67.1, C68.2, C69.2, C70.2, C71.2, C72.2, C73.2, C74.2, C75.2, C76.2, C77.1, C78.1, C79.2, C80.2, C81.2, C82.2, C83.2, C84.2, C85.2, C86.2, C87.2, C88.1, C89.1, C92.2, C93.2, C94.2, C95.2, C96.2, C97.2, C98.2, C99.1, C100.1, C103.2, C104.2, C105.2, C106.2, C107.2, C108.2, C109.2, C110.1, C111.1, C112.2, C113.2, C114.2, C115.2, C116.2, C117.2, C118.2, C119.2, C120.2, C121.1, C122.1, C123.2, C124.2, C125.2, C126.2, C132.2, C133.2, C134.1, C135.2, C136.2, C137.2, C138.2, C139.1, C140.2, C141.2, C142.2, C143.2, C144.2, C145.2, C274.2, C275.2, C276.2, C279.2, C280.2, C281.2, C282.2, C283.2, C284.2, C285.2, C286.2, C287.2, C288.2, C289.2, C290.2, C291.2, C292.2, C293.2, C294.2, C295.2, C296.2, C297.2, C298.2, C299.2, C300.2, C301.2, C302.2, C303.2, C304.2, C305.2, C306.2, C307.2, C308.2, C309.2, C310.2, C311.2, C312.2, C313.2, C314.2, C316.2, C317.2, C318.2, C319.2, C322.2, C323.2, C324.2, C325.2, C328.2, C329.2, C330.2, C331.2, C334.2, C336.2, C337.2, C338.2, C339.2, C340.2, C341.2, C342.2, C343.2, C344.2, C346.2, C347.2, C348.2, C349.2, C351.2, C352.2, C353.2, C354.2, C356.2, C357.2, C358.2, C360.2, C361.2, C362.2, C363.2, C364.2, C365.2, C366.2, C367.2, C368.2, C369.2, C370.2, C371.2, C372.2, C373.2, C374.2, C375.2, C376.2, C377.2, C378.2, C379.2, C380.2, C381.2, C382.2, C383.2, C384.2, C385.2, C386.2, C387.2, C388.2, C389.2, C390.2, C391.2, C392.2, C393.2, C394.2, C395.2, C397.2, C398.2, C399.2, C400.2, C402.2, C403.2, C404.2, C405.2, C407.2, C408.2, C409.2, C410.2, C412.2, C413.2, C414.2, C415.2, C416.2, C417.2, C418.2, C419.2, C420.2, C421.2, C422.2, C423.2, C424.2, C425.2, C426.2, C427.2, C428.2, C429.2, C430.2, C431.2, J1.1, J1.4, J1.5, J1.8, J1.9, J1.12, J1.13, J1.16, J1.17, J1.20, J1.21, J1.24, J1.25, J1.28, J1.29, J1.32, J1.33, J1.36, J1.38, J1.40, J1.42, J1.43, J1.46, J1.47, J1.50, J1.53, J1.56, J1.59, J1.62, J1.65, J1.68, J1.75, J1.77, J1.79, J1.81, J1.84, J1.85, J1.88, J1.91, J1.94, J1.97, J1.100, J1.103, J1.106, J1.109, J1.112, J1.115, J1.118, J1.120, J1.123, J1.126, J1.129, J1.132, J1.135, J1.138, J1.141, J1.144, J1.147, J1.150, J1.153, J1.156, J1.159, J2.2, J2.3, J2.4, J2.5, J3.2, J3.3, J3.4, J3.5, J4.2, J4.3, J4.4, J4.5, J5.2, J5.3, J5.4, J5.5, J9.1, J10.1, JP8.2, JP84.2, JP85.2, JP98.2, JP99.2, JP130.1, JP131.1, JP134.1, JP135.1, JP136.1, JP137.1, JP166.1, JP166.2, JP167.1, JP167.2, JP189.1, JP189.2, JP190.1, JP190.2, JP212.1, JP212.2, JP213.1, JP213.2, JP218.1, JP219.1, JP241.1, JP242.1, JP259.2, JP264.1, JP265.1, JP281.2, JP287.1, JP288.1, JP304.2, JP310.1, JP311.1, JP327.2, JP333.1, JP334.1, JP392.2, JP399.2, JP418.1, JP419.1, JP427.2, JP436.2, JP439.2, JP442.1, JP445.1, R5.1, R8.1, R89.1, R93.1, R97.1, R101.1, R102.1, R103.2, R103.3, R104.2, R104.3, R105.1, R106.1, R107.2, R107.3, R108.2, R108.3, R117.1, R118.1, R119.2, R119.3, R120.2, R120.3, R121.1, R122.1, R123.2, R123.3, R124.2, R124.3, R127.1, R128.2, R128.3, R129.1, R130.2, R130.3, R132.1, R134.1, R168.2, R171.2, R173.2, R175.2, R177.1, R178.2, R178.3, R179.2, R179.3, R221.2, R222.2, U4.2 (NC), U4.3 (NC), U4.4 (NC), U4.12 (GND), U4.13 (NC), U4.14 (NC), U4.17 (NC), U4.21 (PAD), U5.2 (NC), U5.3 (NC), U5.4 (NC), U5.12 (GND), U5.13 (NC), U5.14 (NC), U5.17 (NC), U5.21 (PAD), U7.4 (GND), U7.10 (GND), U7.15 (GND), U7.21 (GND), U7.28 (GND), U7.34 (GND), U7.39 (GND), U7.45 (GND), U8.4 (GND), U8.10 (GND), U8.15 (GND), U8.21 (GND), U8.28 (GND), U8.34 (GND), U8.39 (GND), U8.45 (GND), U10.8 (GND), U10.9 (GND), U10.17 (EPAD), U20.3 (GND), U20.6 (~OE), U20.12 (~FLT), U23.3 (GND), U23.6 (~OE), U23.12 (~FLT), U26.3 (GND), U26.6 (~OE), U26.12 (~FLT), U29.3 (GND), U29.6 (~OE), U29.12 (~FLT), U32.3 (GND), U32.6 (~OE), U32.12 (~FLT), U35.3 (GND), U35.6 (~OE), U35.12 (~FLT), U41.2 (NC), U41.3 (NC), U41.4 (NC), U41.12 (GND), U41.13 (NC), U41.14 (NC), U41.17 (NC), U41.21 (PAD), U42.2 (NC), U42.3 (NC), U42.4 (NC), U42.12 (GND), U42.13 (NC), U42.14 (NC), U42.17 (NC), U42.21 (PAD), U43.2 (NC), U43.3 (gnda), U43.4 (NC), U43.6 (NC), U43.8 (NC), U43.10 (NC), U43.16 (NC), U43.18 (NC), U43.20 (NC), U43.21 (gnda), U43.22 (NC), U43.24 (NC), U43.29 (AIN<3>), U43.33 (AIN<7>), U43.38 (gnda), U43.52 (NC), U43.54 (NC), U43.55 (gnda), U43.56 (NC), U43.58 (NC), U43.60 (NC), U43.66 (NC), U43.68 (NC), U43.70 (NC), U43.72 (NC), U43.73 (gnda), U43.74 (Nc), U43.82 (gnda), U43.89 (gnda), U43.99 (gnda), U43.101 (THERM), U44.7 (IMONN), U44.10 (GND)
unnamed: C3.2, JP258.2, JP392.1, JP393.1, R2.2, R2.3
unnamed: C6.1, JP15.1
unnamed: C10.2, JP304.1, JP396.1, JP397.2, R4.2, R4.3
unnamed: C11.1, JP21.1
unnamed: C16.1, JP66.2, U8.7 (VCCB)
unnamed: C17.1, JP67.2, U8.18 (VCCB)
unnamed: C18.1, JP108.2, U8.42 (VCCA)
unnamed: C19.1, JP109.2, U8.31 (VCCA)
unnamed: C20.1, JP105.2, U7.31 (VCCA)
unnamed: C21.1, JP104.2, U7.42 (VCCA)
unnamed: C22.1, JP102.2, U7.7 (VCCB)
unnamed: C23.1, JP103.2, U7.18 (VCCB)
unnamed: C35.2, JP259.1, JP394.1, JP395.2, R91.2, R91.3
unnamed: C37.1, JP163.1
unnamed: C46.2, JP281.1, JP282.1, JP305.2, R95.2, R95.3
unnamed: C47.2, JP327.1, JP328.1, JP398.2, R96.2, R96.3
unnamed: C48.1, JP186.1
unnamed: C49.1, JP187.1
unnamed: C57.2, JP399.1, JP406.1, JP417.2, R99.2, R99.3
unnamed: C59.1, JP209.1
unnamed: C70.1, JP232.1
unnamed: C71.1, JP233.1
unnamed: C81.1, JP255.1
unnamed: C82.1, JP256.1
unnamed: C90.2, JP8.1, JP9.1, JP426.2, R111.2, R111.3
unnamed: C91.2, JP436.1, JP437.1, JP438.2, R112.2, R112.3
unnamed: C92.1, JP278.1
unnamed: C93.1, JP279.1
unnamed: C101.2, JP427.1, JP428.1, JP429.2, R115.2, R115.3
unnamed: C102.2, JP439.1, JP440.1, JP441.2, R116.2, R116.3
unnamed: C103.1, JP301.1
unnamed: C104.1, JP302.1
unnamed: C114.1, JP324.1
unnamed: C115.1, JP325.1
unnamed: C125.1, JP347.1
unnamed: C126.1, JP348.1
unnamed: C136.1, JP362.1
unnamed: C141.1, JP369.1
unnamed: C336.1, C340.1, C348.1, C353.1, JP430.1, JP431.1, R193.2
unnamed: C337.1, C346.1, C351.1, C356.1, JP432.1, JP433.1, R194.2
unnamed: C338.1, C347.1, C352.1, C357.1, JP434.1, JP435.1, R195.2
unnamed: JP34.2, R9.1
unnamed: JP35.2, R10.1
unnamed: JP36.2, R11.1
unnamed: JP37.2, R12.1
unnamed: JP38.2, R13.1
unnamed: JP39.2, R14.1
unnamed: JP40.2, R15.1
unnamed: JP41.2, R16.1
unnamed: JP42.2, R17.1
unnamed: JP43.2, R18.1
unnamed: JP44.2, R19.1
unnamed: JP45.2, R20.1
unnamed: JP46.2, R21.1
unnamed: JP47.2, R22.1
unnamed: JP48.2, R23.1
unnamed: JP49.2, R24.1
unnamed: JP50.1, R25.2
unnamed: JP51.1, R26.2
unnamed: JP52.1, R27.1
unnamed: JP53.1, R28.2
unnamed: JP54.1, R29.2
unnamed: JP55.1, R30.2
unnamed: JP56.1, R31.2
unnamed: JP57.1, R32.2
unnamed: JP58.1, R33.2
unnamed: JP59.1, R34.2
unnamed: JP60.1, R35.2
unnamed: JP61.1, R36.2
unnamed: JP62.1, R37.2
unnamed: JP63.1, R38.2
unnamed: JP64.1, R39.2
unnamed: JP65.1, R40.2
unnamed: JP68.2, R41.1
unnamed: JP69.2, R42.1
unnamed: JP70.2, R43.1
unnamed: JP71.2, R44.1
unnamed: JP72.2, R45.1
unnamed: JP73.2, R46.1
unnamed: JP74.2, R47.1
unnamed: JP75.2, R48.1
unnamed: JP76.2, R49.1
unnamed: JP77.2, R50.1
unnamed: JP78.2, R51.1
unnamed: JP79.2, R52.1
unnamed: JP80.2, R53.1
unnamed: JP81.2, R54.1
unnamed: JP82.2, R55.1
unnamed: JP83.2, R56.1
unnamed: JP86.1, R57.2
unnamed: JP87.1, R58.2
unnamed: JP88.1, R59.2
unnamed: JP89.1, R60.2
unnamed: JP90.1, R61.2
unnamed: JP91.1, R62.2
unnamed: JP92.1, R63.2
unnamed: JP93.1, R64.2
unnamed: JP94.1, R65.2
unnamed: JP95.1, R66.2
unnamed: JP96.1, R67.2
unnamed: JP97.1, R68.2
unnamed: JP100.1, R69.2
unnamed: JP101.1, R70.2
unnamed: JP106.1, R71.2
unnamed: JP107.1, R72.2
unnamed: JP120.2, R81.1
unnamed: JP121.2, R82.1
unnamed: JP122.2, R83.1
unnamed: JP123.2, R84.1
unnamed: JP125.2, R85.1
unnamed: JP126.2, R86.1
unnamed: JP127.2, R87.1
unnamed: JP128.2, R88.1
unnamed: JP258.1, R167.1
unnamed: JP305.1, R90.1
unnamed: JP395.1, R170.1
unnamed: JP397.1, R169.1
unnamed: JP398.1, R172.1
unnamed: JP417.1, R98.1
unnamed: JP418.2, R113.1, R171.1
unnamed: JP419.2, R114.1, R173.1
unnamed: JP426.1, R218.1
unnamed: JP429.1, R217.1
unnamed: JP438.1, R219.1
unnamed: JP441.1, R220.1
unnamed: JP442.2, R110.1, R221.1
unnamed: JP445.2, R109.1, R222.1
unnamed: R1.1, R168.1
unnamed: R3.1, R175.1
unnamed: R94.1, R177.2
unnamed: R187.2, U43.100 (VDAC)
unnamed: R199.1, U43.83 (VDAC)
unnamed: R200.1, U43.47 (VDAC)
unnamed: C13.1, U4.15 (SS)
unnamed: C15.1, U5.15 (SS)
unnamed: R25.1, U7.47 (1A1)
unnamed: R26.1, U7.46 (1A2)
unnamed: R27.2, U7.44 (1A3)
unnamed: R28.1, U7.43 (1A4)
unnamed: R29.1, U7.41 (1A5)
unnamed: R30.1, U7.40 (1A6)
unnamed: R31.1, U7.38 (1A7)
unnamed: R32.1, U7.37 (1A8)
unnamed: R9.2, U7.2 (1B1)
unnamed: R10.2, U7.3 (1B2)
unnamed: R11.2, U7.5 (1B3)
unnamed: R12.2, U7.6 (1B4)
unnamed: R13.2, U7.8 (1B5)
unnamed: R14.2, U7.9 (1B6)
unnamed: R15.2, U7.11 (1B7)
unnamed: R16.2, U7.12 (1B8)
unnamed: JP134.2, U7.1 (1DIR)
unnamed: R33.1, U7.36 (2A1)
unnamed: R34.1, U7.35 (2A2)
unnamed: R35.1, U7.33 (2A3)
unnamed: R36.1, U7.32 (2A4)
unnamed: R37.1, U7.30 (2A5)
unnamed: R38.1, U7.29 (2A6)
unnamed: R39.1, U7.27 (2A7)
unnamed: R40.1, U7.26 (2A8)
unnamed: R17.2, U7.13 (2B1)
unnamed: R18.2, U7.14 (2B2)
unnamed: R19.2, U7.16 (2B3)
unnamed: R20.2, U7.17 (2B4)
unnamed: R21.2, U7.19 (2B5)
unnamed: R22.2, U7.20 (2B6)
unnamed: R23.2, U7.22 (2B7)
unnamed: R24.2, U7.23 (2B8)
unnamed: JP135.2, U7.24 (2DIR)
unnamed: JP98.1, U7.48 (~1OE)
unnamed: JP99.1, U7.25 (~2OE)
unnamed: R57.1, U8.47 (1A1)
unnamed: R58.1, U8.46 (1A2)
unnamed: R59.1, U8.44 (1A3)
unnamed: R60.1, U8.43 (1A4)
unnamed: R61.1, U8.41 (1A5)
unnamed: R62.1, U8.40 (1A6)
unnamed: R63.1, U8.38 (1A7)
unnamed: R64.1, U8.37 (1A8)
unnamed: R41.2, U8.2 (1B1)
unnamed: R42.2, U8.3 (1B2)
unnamed: R43.2, U8.5 (1B3)
unnamed: R44.2, U8.6 (1B4)
unnamed: R45.2, U8.8 (1B5)
unnamed: R46.2, U8.9 (1B6)
unnamed: R47.2, U8.11 (1B7)
unnamed: R48.2, U8.12 (1B8)
unnamed: JP137.2, U8.1 (1DIR)
unnamed: R65.1, U8.36 (2A1)
unnamed: R66.1, U8.35 (2A2)
unnamed: R67.1, U8.33 (2A3)
unnamed: R68.1, U8.32 (2A4)
unnamed: R69.1, U8.30 (2A5)
unnamed: R70.1, U8.29 (2A6)
unnamed: R71.1, U8.27 (2A7)
unnamed: R72.1, U8.26 (2A8)
unnamed: R49.2, U8.13 (2B1)
unnamed: R50.2, U8.14 (2B2)
unnamed: R51.2, U8.16 (2B3)
unnamed: R52.2, U8.17 (2B4)
unnamed: R53.2, U8.19 (2B5)
unnamed: R54.2, U8.20 (2B6)
unnamed: R55.2, U8.22 (2B7)
unnamed: R56.2, U8.23 (2B8)
unnamed: JP136.2, U8.24 (2DIR)
unnamed: JP84.1, U8.48 (~1OE)
unnamed: JP85.1, U8.25 (~2OE)
unnamed: R88.2, U10.4 (1A1)
unnamed: R87.2, U10.5 (1A2)
unnamed: R84.2, U10.13 (1B1)
unnamed: R83.2, U10.12 (1B2)
unnamed: JP141.2, U10.2 (1DIR)
unnamed: R86.2, U10.6 (2A1)
unnamed: R85.2, U10.7 (2A2)
unnamed: R82.2, U10.11 (2B1)
unnamed: R81.2, U10.10 (2B2)
unnamed: JP140.2, U10.3 (2DIR)
unnamed: C27.1, JP129.2, U10.1 (VCCA)
unnamed: C26.1, JP124.2, U10.16 (VCCB)
unnamed: JP130.2, U10.15 (~1OE)
unnamed: JP131.2, U10.14 (~2OE)
unnamed: JP225.1, U20.11 (COM1)
unnamed: JP226.2, U20.7 (COM2)
unnamed: JP218.2, U20.2 (NO1)
unnamed: JP219.2, U20.4 (NO2)
unnamed: JP384.1, U20.1 (SEL1), U20.5 (SEL2)
unnamed: C65.1, JP211.2, U20.9 (VCC)
unnamed: JP248.1, U23.11 (COM1)
unnamed: JP249.2, U23.7 (COM2)
unnamed: JP241.2, U23.2 (NO1)
unnamed: JP242.2, U23.4 (NO2)
unnamed: JP385.1, U23.1 (SEL1), U23.5 (SEL2)
unnamed: C76.1, JP234.2, U23.9 (VCC)
unnamed: JP271.1, U26.11 (COM1)
unnamed: JP272.2, U26.7 (COM2)
unnamed: JP264.2, U26.2 (NO1)
unnamed: JP265.2, U26.4 (NO2)
unnamed: JP387.1, U26.1 (SEL1), U26.5 (SEL2)
unnamed: C87.1, JP257.2, U26.9 (VCC)
unnamed: JP294.1, U29.11 (COM1)
unnamed: JP295.2, U29.7 (COM2)
unnamed: JP287.2, U29.2 (NO1)
unnamed: JP288.2, U29.4 (NO2)
unnamed: JP388.1, U29.1 (SEL1), U29.5 (SEL2)
unnamed: C98.1, JP280.2, U29.9 (VCC)
unnamed: JP317.1, U32.11 (COM1)
unnamed: JP318.2, U32.7 (COM2)
unnamed: JP310.2, U32.2 (NO1)
unnamed: JP311.2, U32.4 (NO2)
unnamed: JP389.1, U32.1 (SEL1), U32.5 (SEL2)
unnamed: C109.1, JP303.2, U32.9 (VCC)
unnamed: JP340.1, U35.11 (COM1)
unnamed: JP341.2, U35.7 (COM2)
unnamed: JP333.2, U35.2 (NO1)
unnamed: JP334.2, U35.4 (NO2)
unnamed: JP390.1, U35.1 (SEL1), U35.5 (SEL2)
unnamed: C120.1, JP326.2, U35.9 (VCC)
unnamed: C143.1, U41.15 (SS)
unnamed: C145.1, U42.15 (SS)
unnamed: R188.2, U43.26 (AIN<0>)
unnamed: R189.2, U43.27 (AIN<1>)
unnamed: R191.2, U43.28 (AIN<2>)
unnamed: R193.1, U43.30 (AIN<4>)
unnamed: R194.1, U43.31 (AIN<5>)
unnamed: R195.1, U43.32 (AIN<6>)
unnamed: R180.2, U43.14 (VB<0>)
unnamed: R181.2, U43.15 (VB<1>)
unnamed: R182.2, U43.17 (VB<2>)
unnamed: R183.2, U43.19 (VB<3>)

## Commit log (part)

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2025-06-02 Initial commit; Schematic - individual ckts done
2025-06-03 Added QFN100 symbol/footprint - yet to update it
2025-06-04 Added Digial Blocks (Yet to rename fully)
2025-06-04 All dig LS - Labelled
2025-06-04 Digital Fully Done
2025-06-04 calib circuits LS done
2025-06-05 All LS added
2025-06-05 Added IMC chip
2025-06-06 Schematic All DONE?
2025-06-07 Updated Chip R
2025-06-07 Generated BOM, updated schematic
2025-06-11 Layout Initiated
2025-06-12 PCB - Dig Placed
2025-06-12 PCB - Analog LS sample
2025-06-12 Analog LS blocks Placement
2025-06-14 Placement done?
2025-06-16 started routing
2025-06-16 analog LS local routing done
2025-06-17 FMC Donegit add .!
2025-06-17 FMC Ground routed
2025-06-19 routed DIG signals to chip
2025-06-19 Analog calib nets routed
2025-06-20 All routed - make thicker traces
2025-06-22 All done?!
2025-06-23 Updated constraints - rerouting
2025-06-23 DRC CLEANgit add .
2025-06-24 Fab Outputs v1
2025-06-27 Corrections after data approval doc
2025-08-04 v2 ready?
2026-05-06 Fixed vddq_gnd_bug
2026-05-18 Layout Modifications
2026-05-20 Final_Sentoff_Design
